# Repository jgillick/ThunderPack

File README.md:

# ThunderPack

A kick-ass microcontroller board with everything you need in a tiny package that fits in your pocket. Integrated battery & power management system, fast ARM microcontroller, USB bootloader, 4 high-power PWM outputs, 12 GPIOs, satisfying pushbutton switch, and more.

After years of wiring together portable LED controllers that all consisted of a lithium battery, charge controller, shitty slide power switch, and an Arduino nano (or similar), I wanted something better. I always found those versions to be janky and fragile -- not to mention concerned that damaging the pouch cell battery might make it explode in my pocket! This board has everything I need with room to expand.

* [Overview](https://github.com/jgillick/ThunderPack/wiki/)
* [Getting started](https://github.com/jgillick/ThunderPack/wiki/Getting-Started)
* [Pins & functions](https://github.com/jgillick/ThunderPack/wiki/Pinout-Details)
* [Example Programs](./examples)
* [Project log](https://hackaday.io/project/161054-lit-fist)

## Features

* Fast 96Mhz 32-bit ARM microcontroller ([STM32F11xx](https://www.st.com/resource/en/datasheet/stm32f411ce.pdf))
* Integrated high power 500mA lithium battery charger
* 4 high-current PWM outputs (1.4 - 2.3A per channel!) with an LED on each for debugging.
* Additional 12 GPIOs (USART, I2C, SPI, USB)
* 16MB onboard flash
* RGB DotStar LED
* Built-in USB
* Tactile on/off switch
* Momentary button with built-in debounce circuit
* Breadboard friendly
* Supports Arduino & CircuitPython.

## Board & Pinout

### v1.2 Compact
The newest & smallest Thunderpack, measuring in at a minuscule 4cm x 1.9cm (1.6 x 0.75 inches)! The PWM pins on this model can each drive 1.4A to ground (common cathode).

[See the full list of pins and details.](https://github.com/jgillick/ThunderPack/wiki/Pinout-Details)

### v1.2 Original
This is the original ThunderPack form factor and has the battery attached right to the circuit board. The PWM pins on this model can each drive 2.3A to ground (common cathode).

[See the full list of pins and details.](https://github.com/jgillick/ThunderPack/wiki/Pinout-Details)

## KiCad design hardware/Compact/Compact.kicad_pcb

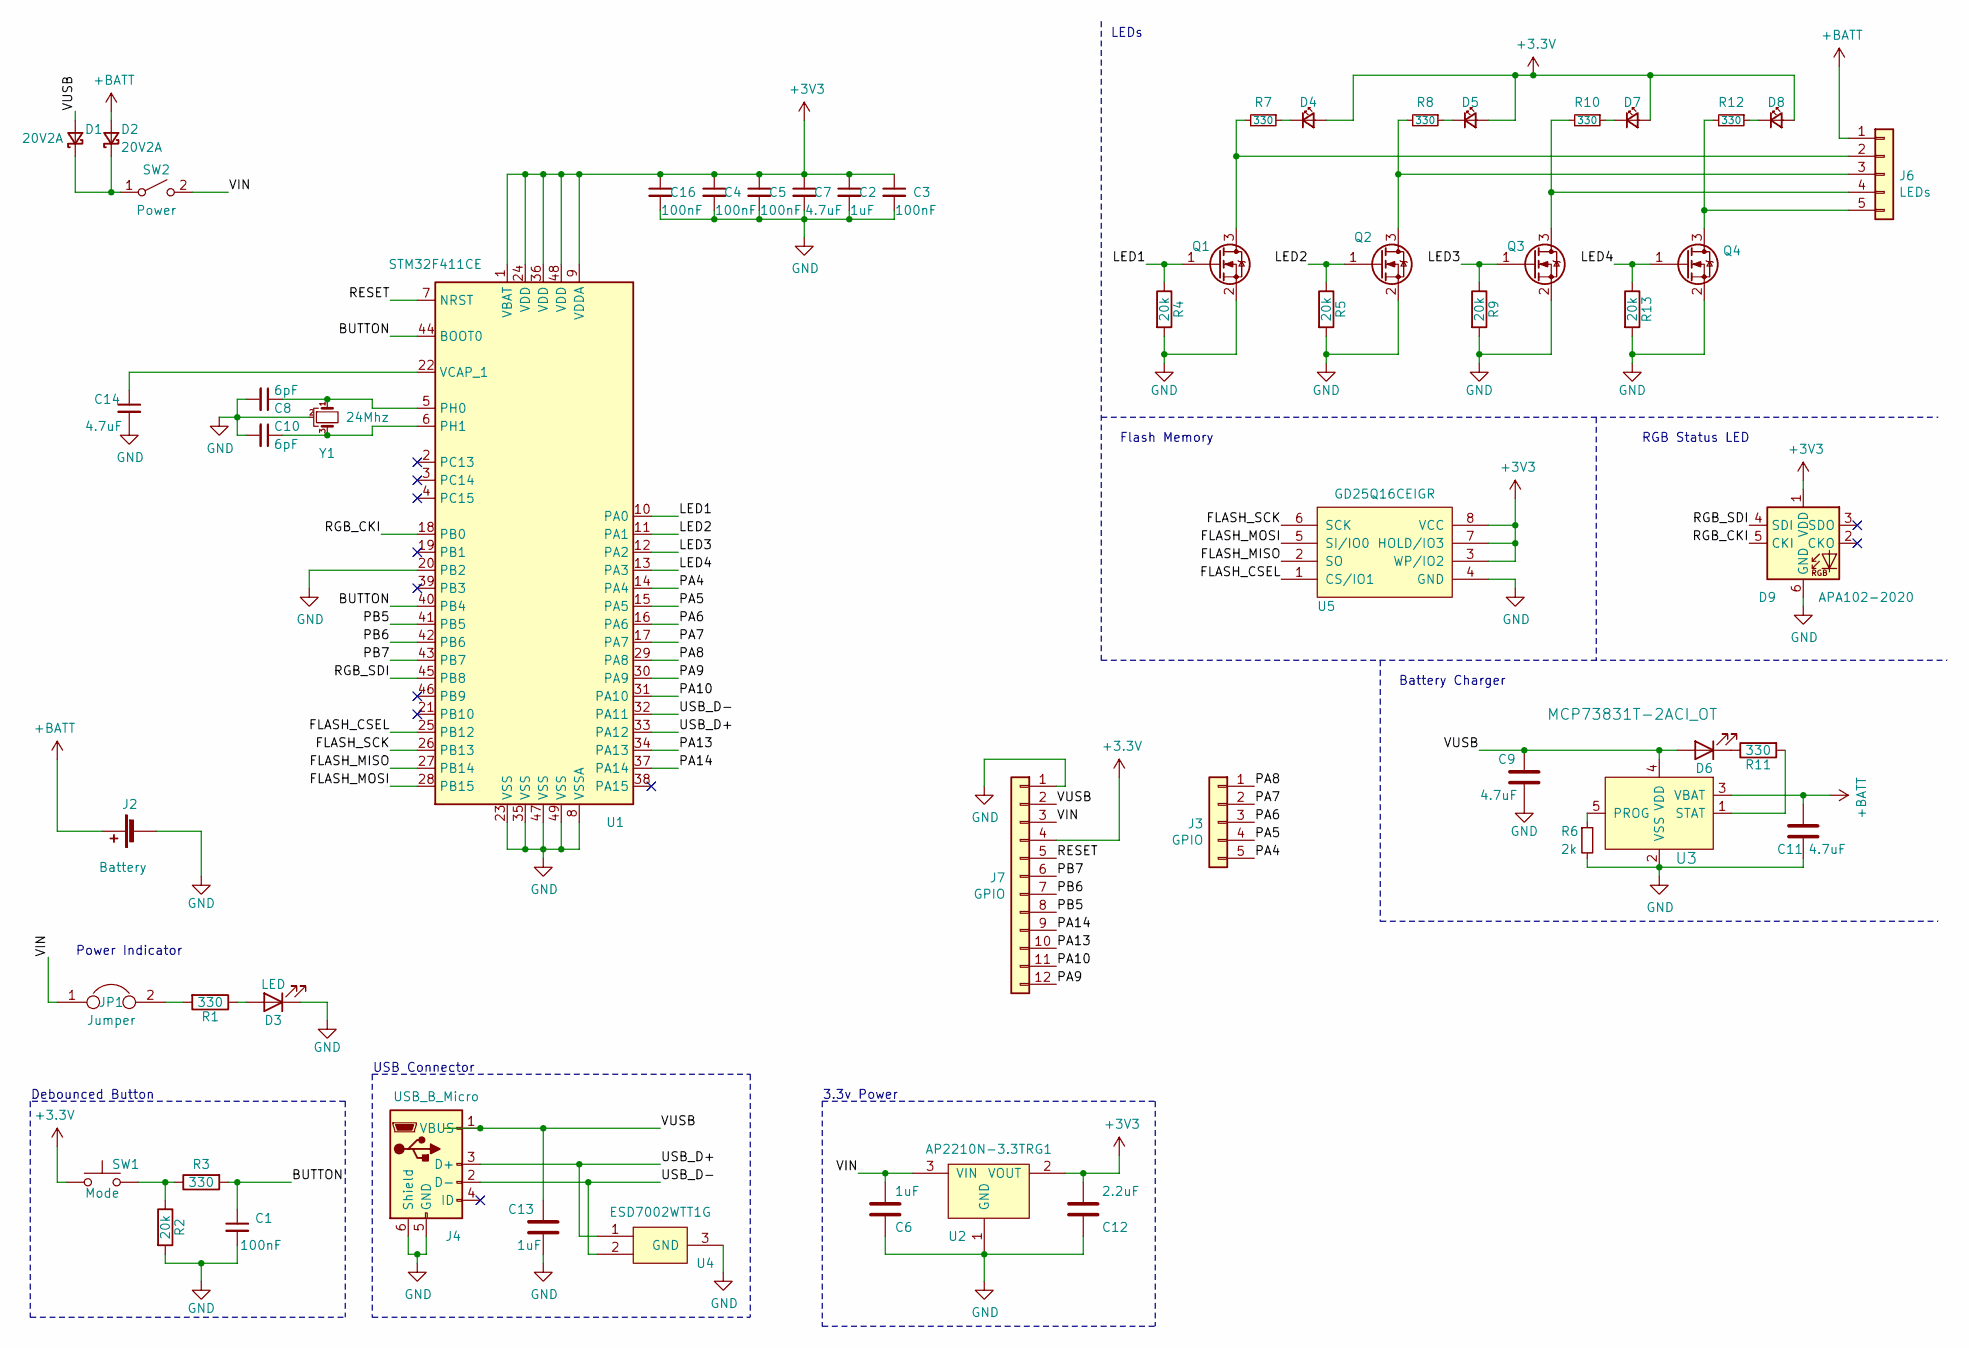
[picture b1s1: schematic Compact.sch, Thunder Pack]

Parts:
C1: 100nF; C_0603_1608Metric; MPN MF-CAP-0603-0.1uF
C2: 1uF; C_0603_1608Metric; MPN MF-CAP-0603-1uF
C3: 100nF; C_0603_1608Metric; MPN Yageo
C4, C5, C16: 100nF; C_0603_1608Metric; MPN 06035C104K4T2A
C6, C13: 1uF; C_0603_1608Metric
C7, C14: 4.7uF; C_0603_1608Metric; MPN CL10A475KO8NNNC‎
C8, C10: 6pF; C_0603_1608Metric; MPN CL10C060CB8NNNC; Digikey 1276-2133-1-ND
C9, C11: 4.7uF; C_0603_1608Metric
C12: 2.2uF; C_0603_1608Metric; MPN CL10A225KO8NNNC
D1, D2: 20V2A; D_SOD-323; MPN SMD22WS-TP
D3: LED; LED_0603_1608Metric_Castellated; MPN 150060BS55040
D4, D5, D7, D8: LED; LED_0603_1608Metric; MPN 150060VS75000
D6: LED; LED_0603_1608Metric; MPN 150060SS75000
D9: APA102-2020; LED-APA102-2020
J2: Battery; JST_PH_S2B-PH-K_1x02_P2.00mm_Horizontal; MPN Keystone 54; Digikey 36-54-ND
J3: GPIO; PinHeader_1x05_P2.54mm_Vertical
J4: USB_B_Micro; USB_Micro-B_Amphenol_10103594-0001LF_Horizontal; MPN 10103594-0001LF
J6: LEDs; PinHeader_1x05_P2.54mm_Vertical
J7: GPIO; PinHeader_1x12_P2.54mm_Vertical
JP1: Jumper; SolderJumper-2_P1.3mm_Bridged_RoundedPad1.0x1.5mm
Q1, Q2, Q3, Q4: BSS806N; SOT-323_SC-70; MPN BSS816NWH6327XTSA1
R1: 330; R_0603_1608Metric
R2, R4, R5, R9, R13: 20k; R_0603_1608Metric; MPN CR0603-FX-2002ELF
R3: 330; R_0603_1608Metric; MPN MF-RES-0603-330
R6: 2k; R_0603_1608Metric; MPN RMCF0603FT2K00
R7, R8, R10, R12: 330; R_0603_1608Metric; MPN CRCW0603270RJNEA
R11: 330; R_0603_1608Metric; MPN ERJ-PA3F4300V
SW1: Mode; SW_SPST_FSMSM; MPN 1437566-3; Digikey 450-1140-ND
SW2: Power; SW_KAN-15_SMD; MPN KAN15
U1: STM32F411CE; QFN-48-1EP_7x7mm_P0.5mm_EP5.6x5.6mm; MPN STM32F411CE
U2: AP2210N-3.3TRG1; SOT-23; MPN AP2210N-3.3TRG1
U3: MCP73831T-2ACI_OT; SOT-23-5; MPN MCP73831T-2ACI/OT; Digi-Key_PN MCP73831T-2ACI/OTCT-ND
U4: ESD7002WTT1G; SOT-323_SC-70
U5: GD25Q16CEIGR; DFN-8-1EP_3x2mm_P0.5mm_EP1.3x1.5mm
Y1: 24Mhz; Crystal_SMD_2016-4Pin_2.0x1.6mm; MPN XRCGB24M000F0L00R0; Digikey 490-5575-1-ND

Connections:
+BATT: C11.1, D2.2 (A), J2.1 (+), J6.1, U3.3 (VBAT)
/BUTTON: C1.1, R3.2, U1.40 (PB4), U1.44 (BOOT0)
/FLASH_CSEL: U1.25 (PB12), U5.1 (CS/IO1)
/FLASH_MISO: U1.27 (PB14), U5.2 (SO)
/FLASH_MOSI: U1.28 (PB15), U5.5 (SI/IO0)
/FLASH_SCK: U1.26 (PB13), U5.6 (SCK)
/LED1: Q1.1 (G), R4.1, U1.10 (PA0)
/LED2: Q2.1 (G), R5.1, U1.11 (PA1)
/LED3: Q3.1 (G), R9.1, U1.12 (PA2)
/LED4: Q4.1 (G), R13.1, U1.13 (PA3)
/PA4: J3.5, U1.14 (PA4)
/PA5: J3.4, U1.15 (PA5)
/PA6: J3.3, U1.16 (PA6)
/PA7: J3.2, U1.17 (PA7)
/PA8: J3.1, U1.29 (PA8)
/PA9: J7.12, U1.30 (PA9)
/PA10: J7.11, U1.31 (PA10)
/PA13: J7.10, U1.34 (PA13)
/PA14: J7.9, U1.37 (PA14)
/PB5: J7.8, U1.41 (PB5)
/PB6: J7.7, U1.42 (PB6)
/PB7: J7.6, U1.43 (PB7)
/RESET: J7.5, U1.7 (NRST)
/RGB_CKI: D9.5 (CKI), U1.18 (PB0)
/RGB_SDI: D9.4 (SDI), U1.45 (PB8)
/USB_D+: J4.3 (D+), U1.33 (PA12), U4.1
/USB_D-: J4.2 (D-), U1.32 (PA11), U4.2
/VIN: C6.1, J7.3, JP1.1, SW2.2 (B), U2.3 (VIN)
/VUSB: C9.1, C13.2, D1.2 (A), D6.2 (A), J4.1 (VBUS), J7.2, U3.4 (VDD)
GND: C1.2, C2.2, C3.2, C4.2, C5.2, C6.2, C7.2, C8.2, C9.2, C10.2, C11.2, C12.2, C13.1, C14.2, C16.2, D3.1 (K), D9.6 (GND), J2.2 (-), J4.5 (GND), J4.6 (Shield), J7.1, Q1.2 (S), Q2.2 (S), Q3.2 (S), Q4.2 (S), R2.2, R4.2, R5.2, R6.2, R9.2, R13.2, U1.8 (VSSA), U1.20 (PB2), U1.23 (VSS), U1.35 (VSS), U1.47 (VSS), U1.49 (VSS), U2.1 (GND), U3.2 (VSS), U4.3 (GND), U5.4 (GND), Y1.2
unnamed: C8.1, U1.5 (PH0), Y1.1
unnamed: C10.1, U1.6 (PH1), Y1.3
unnamed: C14.1, U1.22 (VCAP_1)
unnamed: D1.1 (K), D2.1 (K), SW2.1 (A)
unnamed: D3.2 (A), R1.1
unnamed: D4.1 (K), R7.1
unnamed: D5.1 (K), R8.1
unnamed: D6.1 (K), R11.1
unnamed: D7.1 (K), R10.1
unnamed: D8.1 (K), R12.1
unnamed: J6.2, Q1.3 (D), R7.2
unnamed: J6.3, Q2.3 (D), R8.2
unnamed: J6.4, Q3.3 (D), R10.2
unnamed: J6.5, Q4.3 (D), R12.2
unnamed: JP1.2, R1.2
unnamed: R2.1, R3.1, SW1.2
unnamed: R6.1, U3.5 (PROG)
unnamed: R11.2, U3.1 (STAT)

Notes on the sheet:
Battery Charger
USB Connector
LEDs
3.3v Power
Power Indicator
RGB Status LED
Flash Memory
Debounced Button

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
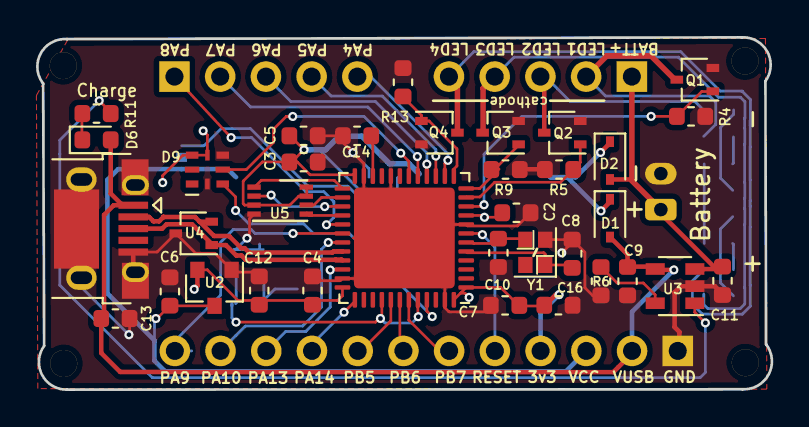
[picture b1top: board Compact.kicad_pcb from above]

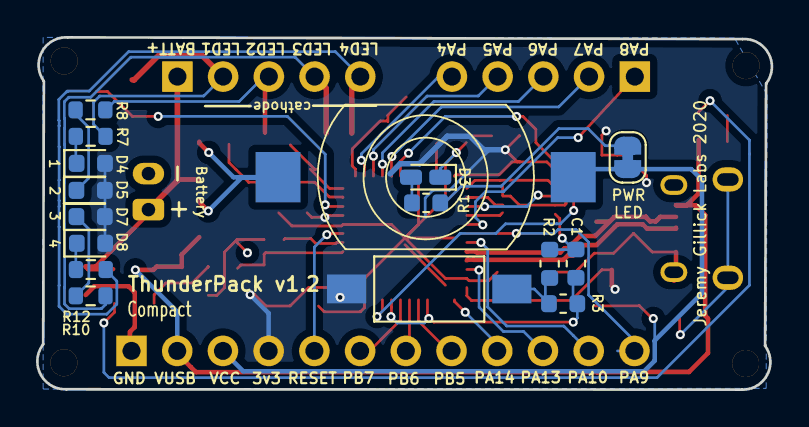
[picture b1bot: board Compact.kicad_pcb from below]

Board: 2 copper layers, 40.8 x 19.6 mm, 55 parts (16 on the bottom side), 49 nets.

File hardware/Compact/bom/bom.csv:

Id,Designator,Manufacturer,Quantity,*Mfg Part #,Value,Package,Description / Value,Type,Notes,
1,U4,ON Semiconductor,1,ESD7002WTT1G,,SOT-323_SC-70,TVS DIODE 5V SC70-3,SMD,,
2,D9,SparkFun Electronics,1,APA102-2020,,LED-APA102-2020,ADDRESS LED STRIP SER RGB 10PK,SMD,,
3,J2,TE Connectivity,1,440055-2,,JST_PH_S2B-PH-K_1x02_P2.00mm_Horizontal,"Connector Header Through Hole, Right Angle 2 position 0.079"" (2.00mm)",thru-hole,,
4,"R12,R10,R8,R7,R3,R11,R1",,7,,330,0603,RES SMD 330 OHM 0.5% 1/5W 0603,SMD,,
5,D6,Würth Elektronik,1,150060SS75000,,0603,LED RED CLEAR 0603 SMD,SMD,,
6,"D8,D7,D5,D4",Würth Elektronik,4,150060VS75000,,0603,LED GREEN CLEAR 0603 SMD,SMD,,
7,"D1,D2",Micro Commercial Co,2,SMD22WS-TP,,SOD-323,"2A,20V,SCHOTTKY,SOD-323 PACKAGE",SMD,,
8,SW1,TE Connectivity,1,FSMSM,,,SWITCH TACTILE SPST-NO 0.05A 24V,SMD,,
9,U5,GigaDevice Semiconductor,1,GD25Q16CEIGR,,8-XFDFN,FLASH - NOR Memory IC 16Mb (2M x 8) SPI - Quad I/O 120MHz 8-USON (2x3),SMD,,
10,U1,STMicroelectronics,1,STM32F411CEU6,,48-UFQFN,IC MCU 32BIT 512KB FLSH 48UFQFPN,SMD,,
11,"Q2,Q4,Q3,Q1",Infineon Technologies,4,BSS816NWH6327XTSA1,,SOT-323,MOSFET N-CH 20V 1.4A SOT323-3,SMD,,
12,"R13,R9,R5,R4,R2",,5,,20k,0603,RES SMD 20K OHM 0.5% 1/10W 0603,SMD,,
13,"C1,C4,C16,C5,C3",,5,,100nF,0603,CAP CER 0.1UF 50V X7R 0603,SMD,,
14,U3,Microchip Technology,1,MCP73831T-2ACI/OT,,SOT-23-5,IC BATT CNTL LI-ION 1CEL SOT23-5,SMD,,
15,R6,,1,,2k,0603,RES 2K OHM 1% 1/10W 0603,SMD,,
16,"C11,C9,C14,C7",,4,,4.7uF,0603,CAP CER 4.7UF 16V X5R 0603,SMD,,
17,D3,Würth Elektronik,1,150060BS55040,,0603,LED BLUE DIFFUSED 0603 SMD,SMD,,
18,C12,,1,,2.2uF,0603,CAP CER 2.2UF 16V X5R 0603,SMD,,
19,Y1,XRCGB24M000F0L00R0,1,24Mhz,,4-SMD,CRYSTAL 24.0000MHZ 6PF SMD,SMD,,
20,U2,Diodes Incorporated,1,AP2210N-3.3TRG1,,SOT-23-3,IC REG LINEAR 3.3V 300MA SOT23-3,SMD,,
21,J4,Amphenol ICC (FCI),1,10103594-0001LF,,,CONN RCPT USB2.0 MICRO B SMD R/A,SMD,,
22,"C13,C6,C2",,3,,1uF,0603,CAP CER 1UF 25V X5R 0603,SMD,,
23,"C10,C8",,2,,6pF,0603,CAP CER 6PF 50V C0G/NP0 0603,SMD,,

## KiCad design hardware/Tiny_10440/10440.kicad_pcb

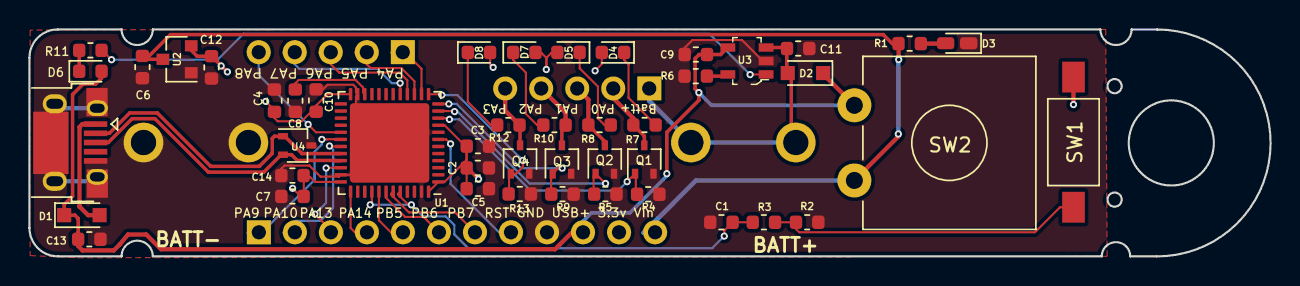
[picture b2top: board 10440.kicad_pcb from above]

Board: 2 copper layers, 87.5 x 16.0 mm, 50 parts (0 on the bottom side), 40 nets.

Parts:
C1: 100nF; C_0603_1608Metric
C2, C6, C13: 1uf; C_0603_1608Metric
C3, C4, C5, C10, C14: 100nf; C_0603_1608Metric
C7, C8, C9, C11: 4.7uF; C_0603_1608Metric
C12: 2.2uF; C_0603_1608Metric
D1, D2: 20V2A; D_SOD-323_HandSoldering
D3: LED; LED_0603_1608Metric_Castellated
D4, D5, D6, D7, D8: LED; LED_0603_1608Metric
J2: Battery; MDP_BK-82_10440
J3: GPIO; PinHeader_1x05_P2.54mm_Vertical
J4: USB_B_Micro; USB_Micro-B_Amphenol_10103594-0001LF_Horizontal
J5: LEDs; PinHeader_1x05_P2.54mm_Vertical
J7: GPIO/Power; PinHeader_1x12_P2.54mm_Vertical
Q1, Q2, Q3, Q4: BSS806N; SOT-323_SC-70
R1, R7, R8, R10, R12: 270; R_0603_1608Metric
R2: 20K; R_0603_1608Metric
R3, R11: 330; R_0603_1608Metric
R4, R5, R9, R13: 20k; R_0603_1608Metric
R6: 675; R_0603_1608Metric
SW1: Mode; SW_SPST_FSMSM
SW2: Power; SW_CW_GPTS203211B
U1: STM32F412CGUx; QFN-48-1EP_7x7mm_P0.5mm_EP5.6x5.6mm
U2: AP2210N-3.3TRG1; SOT-23
U3: MCP73831T-2ACI_OT; SOT-753
U4: ESD7002WTT1G; SOT-323_SC-70

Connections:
+3V3: C2.1, C3.1, C4.1, C5.1, C7.1, C10.1, C12.1, C14.1, D4.2, D5.2, D7.2, D8.2, J7.11, SW1.1, U1.1, U1.9, U1.24, U1.36, U1.48, U2.2
+BATT: C11.1, D2.2, J2.1, J5.1, U3.3
/BUTTON: C1.1, R3.2, U1.40, U1.44
/LED1: J5.2, Q1.3, R7.2
/LED2: J5.3, Q2.3, R8.2
/LED3: J5.4, Q3.3, R10.2
/LED4: J5.5, Q4.3, R12.2
/PA4: J3.1, U1.14
/PA5: J3.2, U1.15
/PA6: J3.3, U1.16
/PA7: J3.4, U1.17
/PA8: J3.5, U1.29
/PA9: J7.1, U1.30
/PA10: J7.2, U1.31
/PA13: J7.3, U1.34
/PA14: J7.4, U1.37
/PB5: J7.5, U1.41
/PB6: J7.6, U1.42
/PB7: J7.7, U1.43
/PWM1: Q1.1, R4.1, U1.10
/PWM2: Q2.1, R5.1, U1.11
/PWM3: Q3.1, R9.1, U1.12
/PWM4: Q4.1, R13.1, U1.13
/RESET: J7.8, U1.7
/USB_D+: J4.3, U1.33, U4.2
/USB_D-: J4.2, U1.32, U4.1
/VIN: C6.1, J7.12, R1.2, SW2.2, U2.3
/VUSB: C9.1, C13.2, D1.1, D2.1, D6.2, J7.10, SW2.1, U3.4
GND: C1.2, C2.2, C3.2, C4.2, C5.2, C6.2, C7.2, C8.2, C9.2, C10.2, C11.2, C12.2, C13.1, C14.2, D3.1, J2.2, J4.5, J4.6, J7.9, Q1.2, Q2.2, Q3.2, Q4.2, R2.2, R4.2, R5.2, R6.2, R9.2, R13.2, U1.8, U1.23, U1.35, U1.47, U1.49, U2.1, U3.2, U4.3
unnamed: C8.1, U1.22
unnamed: D1.2, J4.1
unnamed: D3.2, R1.1
unnamed: D4.1, R7.1
unnamed: D5.1, R8.1
unnamed: D6.1, R11.1
unnamed: D7.1, R10.1
unnamed: D8.1, R12.1
unnamed: R2.1, R3.1, SW1.2
unnamed: R6.1, U3.5
unnamed: R11.2, U3.1

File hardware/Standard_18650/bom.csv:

Id,RefDefs,Package,Qty,Value,part number/description,,
1,U1,QFN-48-1EP_7x7mm_P0.5mm_EP5.6x5.6mm,1,,STM32F412CGU6,,
2,R6,603,1,675R,,,
3,J2,,1,,Keystone Electronics 54,,
4,"C1,C16,C15,C4,C3,C5",603,5,100nF,,,
5,"C14,C7",603,2,4.7uF,,,
6,U3,SOT-23-6,1,,BQ21040DBVR,,
7,D6,603,1,,150060BS55040,,
8,"D8,D7,D5,D4",603,4,,150060VS75000,,
9,R14,603,1,10k,,,
10,"R11,R3",603,2,330R,,,
11,"C9,C11,C12,C13,C6,C2",603,4,1uF,,,
12,U4,SOT-323_SC-70,1,,ESD7002WTT1G,,
13,U2,SOT-23,1,,AP2210N-3.3TRG1,,
14,J4,,1,,Amphenol 10103594-0001LF USB micro,,
15,SW2,,1,,GPTS203211B,,
16,SW1,,1,,TE Connectivity FSMSM - SWITCH TACTILE SPST-NO 0.05A 24V,,
17,"D1,D2",D_SOD-323,2,,"2A,20V,SCHOTTKY,SOD-323 PACKAGE",,
18,L1,603,1,Bead,BLM18TG601TN1D - Ferrite bead - 600 Ohms @ 100MHz 1 Ferrite Bead 0603 (1608 Metric) 200mA 450mOhm,,
19,"R1,R7,R8,R10,R12",603,5,270R,,,
20,"R2,R4,R5,R9,R13",603,4,20k,,,
21,"Q1,Q3,Q4,Q2",SOT-23,4,,BSS806NH6327XTSA1,,
22,D3,603,1,,150060SS75000,,

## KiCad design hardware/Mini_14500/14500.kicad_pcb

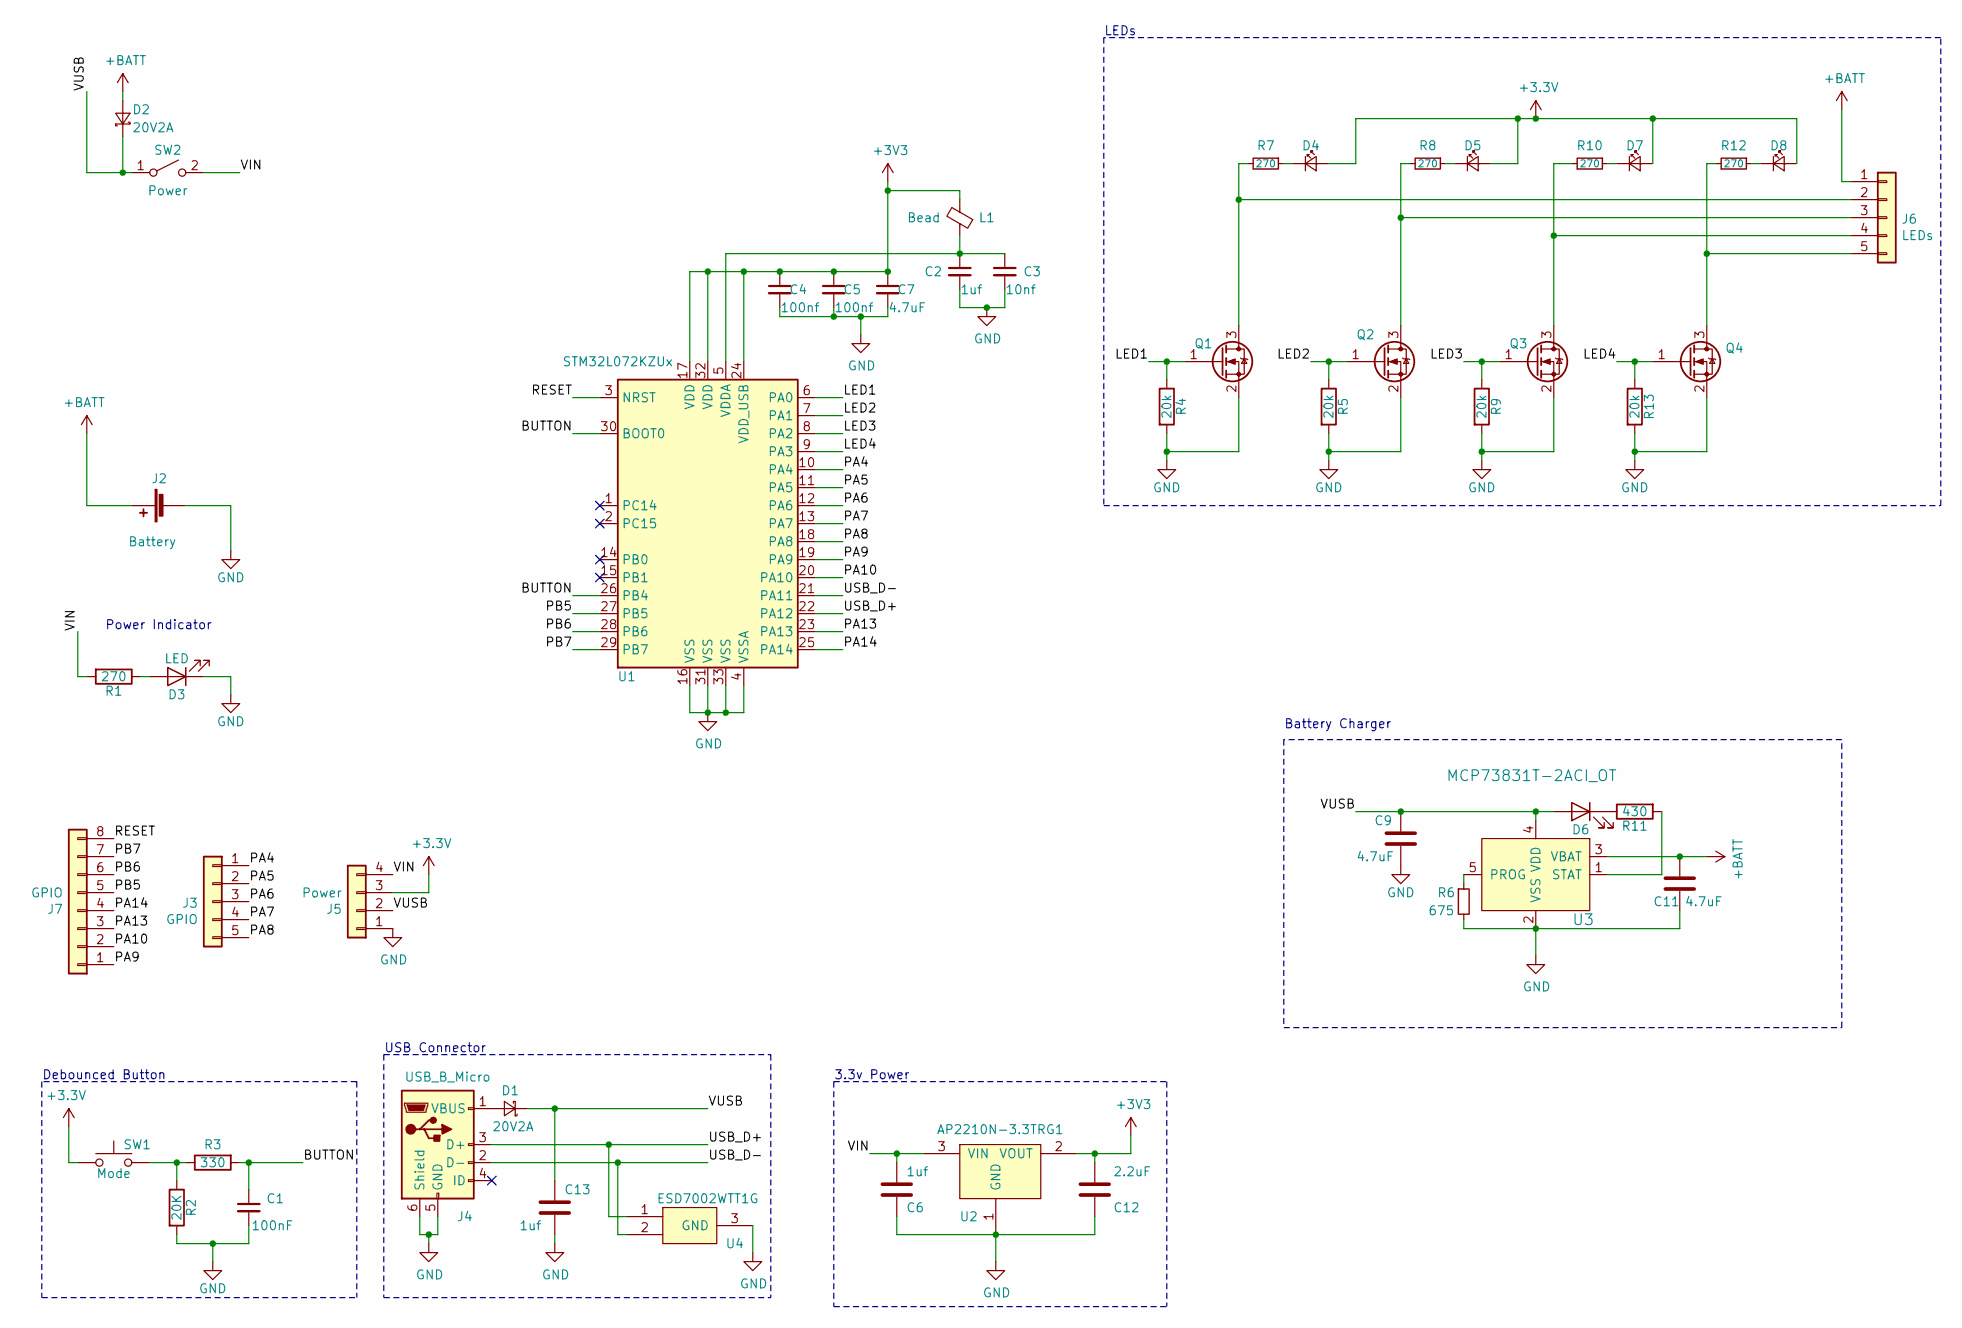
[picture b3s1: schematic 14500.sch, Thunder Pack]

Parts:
C1: 100nF; C_0603_1608Metric; MPN MF-CAP-0603-0.1uF
C2: 1uf; C_0603_1608Metric; MPN MF-CAP-0603-1uF
C3: 10nf; C_0603_1608Metric; MPN Yageo
C4, C5: 100nf; C_0603_1608Metric; MPN 06035C104K4T2A
C6, C13: 1uf; C_0603_1608Metric
C7: 4.7uF; C_0603_1608Metric; MPN CL10A475KO8NNNC‎
C9, C11: 4.7uF; C_0603_1608Metric
C12: 2.2uF; C_0603_1608Metric
D1, D2: 20V2A; D_SOD-323_HandSoldering; MPN SMD22WS-TP
D3: LED; LED_0603_1608Metric_Castellated; MPN 150060SS75000
D4, D5, D7, D8: LED; LED_0603_1608Metric; MPN 150060VS75000
D6: LED; LED_0603_1608Metric; MPN 150060BS55040
J2: Battery; MDP_BK-82_14500; MPN Keystone 54; Digikey 36-54-ND
J3: GPIO; PinHeader_1x05_P2.54mm_Vertical
J4: USB_B_Micro; USB_Micro-B_Amphenol_10103594-0001LF_Horizontal; MPN 10103594-0001LF
J5: Power; PinHeader_1x04_P2.54mm_Vertical
J6: LEDs; PinHeader_1x05_P2.54mm_Vertical
J7: GPIO; PinHeader_1x08_P2.54mm_Vertical
L1: Bead; L_0603_1608Metric; MPN BLM18TG601TN1D; Digikey 490-9702-1-ND
Q1, Q2, Q3, Q4: BSS806N; SOT-23; MPN BSS806NH6327XTSA1
R1: 270; R_0603_1608Metric
R2: 20K; R_0603_1608Metric; MPN CR0603-FX-2002ELF
R3: 330; R_0603_1608Metric; MPN MF-RES-0603-330
R4, R5, R9, R13: 20k; R_0603_1608Metric; MPN CR0603-FX-2002ELF
R6: 675; R_0603_1608Metric
R7, R8, R10, R12: 270; R_0603_1608Metric; MPN CRCW0603270RJNEA
R11: 430; R_0603_1608Metric; MPN ERJ-PA3F4300V
SW1: Mode; SW_SPST_FSMSM; MPN 1437566-3; Digikey 450-1140-ND
SW2: Power; SW_CW_GPTS203211B; MPN GPTS203211B
U1: STM32L072KZUx; QFN-32-1EP_5x5mm_P0.5mm_EP3.45x3.45mm
U2: AP2210N-3.3TRG1; SOT-23; MPN AP2210N-3.3TRG1
U3: MCP73831T-2ACI_OT; SOT-753; MPN MCP73831T-2ACI/OT; Digi-Key_PN MCP73831T-2ACI/OTCT-ND
U4: ESD7002WTT1G; SOT-323_SC-70; MPN ESD7002WTT1G

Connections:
+BATT: C11.1, D2.2 (A), J2.1 (+), J6.1, U3.3 (VBAT)
/BUTTON: C1.1, R3.2, U1.26 (PB4), U1.30 (BOOT0)
/LED1: Q1.1 (G), R4.1, U1.6 (PA0)
/LED2: Q2.1 (G), R5.1, U1.7 (PA1)
/LED3: Q3.1 (G), R9.1, U1.8 (PA2)
/LED4: Q4.1 (G), R13.1, U1.9 (PA3)
/PA4: J3.1, U1.10 (PA4)
/PA5: J3.2, U1.11 (PA5)
/PA6: J3.3, U1.12 (PA6)
/PA7: J3.4, U1.13 (PA7)
/PA8: J3.5, U1.18 (PA8)
/PA9: J7.1, U1.19 (PA9)
/PA10: J7.2, U1.20 (PA10)
/PA13: J7.3, U1.23 (PA13)
/PA14: J7.4, U1.25 (PA14)
/PB5: J7.5, U1.27 (PB5)
/PB6: J7.6, U1.28 (PB6)
/PB7: J7.7, U1.29 (PB7)
/RESET: J7.8, U1.3 (NRST)
/USB_D+: J4.3 (D+), U1.22 (PA12), U4.1
/USB_D-: J4.2 (D-), U1.21 (PA11), U4.2
/VIN: C6.1, J5.4, R1.2, SW2.2 (B), U2.3 (VIN)
/VUSB: C9.1, C13.2, D1.1 (K), D2.1 (K), D6.2 (A), J5.2, SW2.1 (A), U3.4 (VDD)
GND: C1.2, C2.2, C3.2, C4.2, C5.2, C6.2, C7.2, C9.2, C11.2, C12.2, C13.1, D3.1 (K), J2.2 (-), J4.5 (GND), J4.6 (Shield), J5.1, Q1.2 (S), Q2.2 (S), Q3.2 (S), Q4.2 (S), R2.2, R4.2, R5.2, R6.2, R9.2, R13.2, U1.4 (VSSA), U1.16 (VSS), U1.31 (VSS), U1.33 (VSS), U2.1 (GND), U3.2 (VSS), U4.3 (GND)
unnamed: C2.1, C3.1, L1.1, U1.5 (VDDA)
unnamed: D1.2 (A), J4.1 (VBUS)
unnamed: D3.2 (A), R1.1
unnamed: D4.1 (K), R7.1
unnamed: D5.1 (K), R8.1
unnamed: D6.1 (K), R11.1
unnamed: D7.1 (K), R10.1
unnamed: D8.1 (K), R12.1
unnamed: J6.2, Q1.3 (D), R7.2
unnamed: J6.3, Q2.3 (D), R8.2
unnamed: J6.4, Q3.3 (D), R10.2
unnamed: J6.5, Q4.3 (D), R12.2
unnamed: R2.1, R3.1, SW1.2
unnamed: R6.1, U3.5 (PROG)
unnamed: R11.2, U3.1 (STAT)

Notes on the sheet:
Battery Charger
USB Connector
Power Indicator
LEDs
Debounced Button
3.3v Power

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
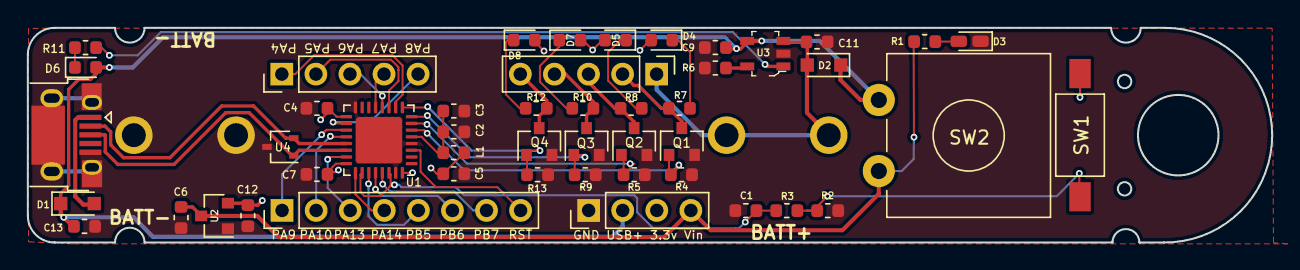
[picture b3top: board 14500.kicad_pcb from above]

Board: 2 copper layers, 92.8 x 16.0 mm, 49 parts (0 on the bottom side), 40 nets.

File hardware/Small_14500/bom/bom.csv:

Id,RefDefs,Package,Qty,Value,part number/description,,
1,Y1,4-SMD,1,24Mhz,XRCGB24M000F0L00R0,,
2,"C16,C15",603,2,6pF,CL10C060CB8NNNC,,
3,R6,603,1,680R,,,
4,D6,603,1,,150060BS55040,,
5,"D8,D7,D5,D4",603,4,,150060VS75000,,
6,"R11,R3",603,2,330R,,,
7,"C11,C8,C9,C7",603,4,4.7uF,CC0603KRX5R5BB475,,
8,U4,SOT-323_SC-70,1,,ESD7002WTT1G,,
9,"C12,C13,C6,C2",603,4,1uf,,,
10,U2,SOT-23,1,,AP2210N-3.3TRG1,,
11,J4,USB_B_Micro,1,,Amphenol 10103594-0001LF,,
12,SW2,Through hole,1,,GPTS203211B,,
13,SW1,Through hole,1,,TE Connectivity FSMSM,,
14,"R2,R4,R5,R9,R13",603,5,20k,,,
15,"R12,R1,R7,R8,R10",603,5,270R,,,
16,"Q3,Q2,Q1,Q4",SOT-23,4,,BSS806N,,
17,D3,603,1,LED,150060SS75000,,
18,"C1,C5,C14,C10,C4,C3",603,6,100nF,,,
19,U1,QFN-48-1EP_7x7mm_P0.5mm_EP5.6x5.6mm,1,,STM32F411CEU6,,
20,U3,SOT-753,1,,MCP73831T-2ACI_OT,,
21,"D1,D2",D_SOD-323,2,20V2A,SMD22WS-TP,,
22,L1,603,1,,BLM18TG601TN1D,,

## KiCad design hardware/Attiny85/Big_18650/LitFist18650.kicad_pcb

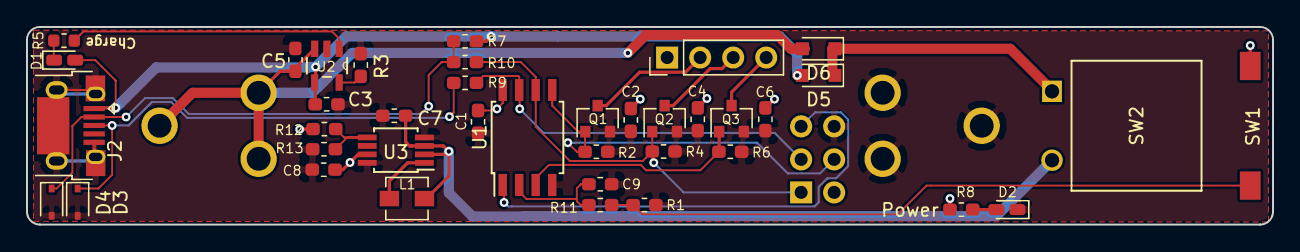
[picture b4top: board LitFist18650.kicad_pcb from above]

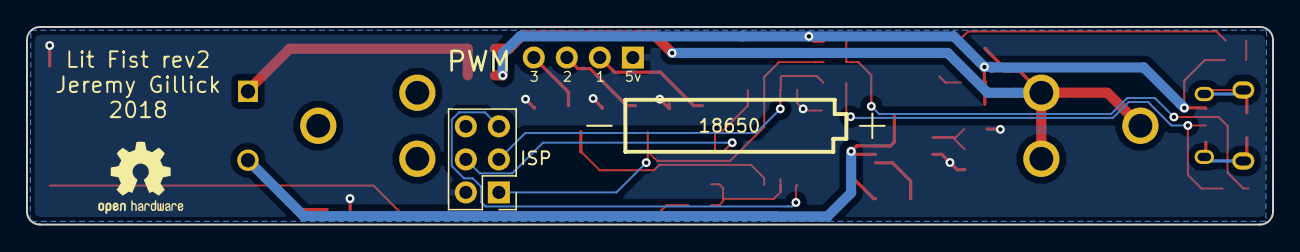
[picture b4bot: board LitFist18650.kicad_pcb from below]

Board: 2 copper layers, 95.8 x 15.2 mm, 41 parts (2 on the bottom side), 24 nets.

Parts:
C1, C9: 0.1uF; C_0603_1608Metric_Pad1.05x0.95mm_HandSolder
C2, C3, C4, C5, C6: 4.7uF; C_0603_1608Metric_Pad1.05x0.95mm_HandSolder
C7: 10uF; C_0603_1608Metric_Pad1.05x0.95mm_HandSolder
C8: 22uF; C_0603_1608Metric_Pad1.05x0.95mm_HandSolder
D1, D2: LED; LED_0603_1608Metric_Castellated
D3, D4: 3v6; D_SOD-323
D5, D6: 20V2A; D_SOD-323_HandSoldering
J1: PWM; PinHeader_1x04_P2.54mm_Vertical
J2: USB_B_Micro; USB_Micro-B_Amphenol_10103594-0001LF_Horizontal
J3: Battery; Battery_Clips_18650
J4: ISP; PinHeader_2x03_P2.54mm_Vertical
L1: 2.2uH3A; L_Vishay_IHLP-1212
Q1, Q2, Q3: NTR4003NT1G; SOT-23
R1: 20K; R_0603_1608Metric_Pad1.05x0.95mm_HandSolder
R2, R4, R6: 20k; R_0603_1608Metric_Pad1.05x0.95mm_HandSolder
R3: 2k; R_0603_1608Metric_Pad1.05x0.95mm_HandSolder
R5: 470; R_0603_1608Metric
R7: 2.2k; R_0603_1608Metric_Pad1.05x0.95mm_HandSolder
R8: 120; R_0603_1608Metric_Pad1.05x0.95mm_HandSolder
R9, R10: 68; R_0603_1608Metric_Pad1.05x0.95mm_HandSolder
R11: 330; R_0603_1608Metric_Pad1.05x0.95mm_HandSolder
R12: 750K; R_0603_1608Metric_Pad1.05x0.95mm_HandSolder
R13: 100K; R_0603_1608Metric_Pad1.05x0.95mm_HandSolder
SW1: Mode; Switch_TE_FSMSM
SW2: Power; Switch_SPST_GPTS203211BR2
U1: ATtiny85-20SU; SOIJ-8_5.3x5.3mm_P1.27mm
U2: MCP73831T-2ACI/OT; SOT95P280X145-5N
U3: PAM2401-8MSOP; MSOP-8_3x3mm_P0.65mm

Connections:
+5V: C1.1, C2.2, C4.2, C6.2, C8.1, J1.1, J4.2, R8.2, R12.1, SW1.2, U1.8, U3.7
+BATT: C5.1, D6.2, J3.1, U2.3
D+: J4.3, R9.1, U1.7
D-: J4.1, Q2.1, R4.1, R10.1, U1.6
GND: C1.2, C2.1, C3.2, C4.1, C5.2, C6.1, C7.2, C8.2, C9.2, D2.1, D3.2, D4.2, J2.5, J2.6, J3.2, J4.6, Q1.2, Q2.2, Q3.2, R1.2, R2.2, R3.2, R4.2, R6.2, R13.2, U1.4, U2.2, U3.4, U3.8
MOSI: J4.4, Q1.1, R2.1, U1.5
unnamed: C7.1, L1.1, SW2.2, U3.2, U3.3
unnamed: C9.1, R11.2, U1.2
unnamed: D1.1, R5.2
unnamed: D2.2, R8.1
unnamed: D3.1, J2.3, R9.2
unnamed: D4.1, J2.2, R7.1, R10.2
unnamed: D5.1, D6.1, SW2.1
unnamed: J1.2, Q1.3
unnamed: J1.3, Q2.3
unnamed: J1.4, Q3.3
unnamed: L1.2, U3.1
unnamed: R1.1, R11.1, SW1.1
unnamed: R3.1, U2.5
unnamed: R5.1, U2.1
unnamed: R12.2, R13.1, U3.5
PWM3: Q3.1, R6.1, U1.3
RST: J4.5, U1.1
Vin: C3.1, D1.2, D5.2, J2.1, R7.2, U2.4

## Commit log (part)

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2018-09-03 Add hardware
2018-09-04 Upgrade to kicad 5
2018-09-13 Populate PCB with ALL THE NEW THINGS
2018-09-13 Remove VCC
2018-09-14 Finish routing
2018-09-14 Adjust routing
2018-09-18 misc
2018-09-18 Move hardware files
2018-09-18 Rename hardware files
2018-09-18 Fix battery number from 8650 to 18650
2018-09-18 misc save
2018-10-22 Fix Attiny footprint. Add debounce circuit.
2018-10-28 Move Attiny version of hardware
2018-10-29 minor save
2018-10-29 Add STM32
2018-10-30 Annotations
2018-10-31 Basic schematic
2018-10-31 Update LED circuit
2019-05-07 PCB for fab
2019-09-06 Update hardware
2019-09-06 Cleanup example & makefile
2019-09-06 Fix ChibiOS name casing.
2019-09-06 Cleanup and docs.
2019-09-07 Update config and docs.
2019-09-07 Move kicad files.
2019-09-07 Docs
2019-09-07 Remove attiny hardware.
2019-09-07 More docs
2019-09-07 Add better description and features section.
2019-09-07 Add blink example.
2019-09-07 Update to use updated board.h definitions.
2019-09-07 Add button example
2019-09-07 Cleanup
2019-09-08 Add 'flash-dfu' make rule.
2019-09-08 Add examples: Fade & RunningLEDs
2019-09-08 Tweak settings.
2019-09-09 Rename LitFist to Thunder Pack
2019-09-09 Ignore more.
2019-09-09 Add arduino support.
2019-09-09 Update LED numbers
2019-09-09 Update features.
2019-09-10 Simplify the Makefile used in each example.
2019-09-10 Add USB serial example.
2019-09-10 Add libopencm3 examples directory
2019-09-10 Add a full 10-pin JTAG connector.
2019-09-11 Change to 32 pin package.
2019-09-11 Add top labels and cleanup.
2019-09-11 Add working libopencm3 examples.
2019-09-11 Update copy.
2019-09-11 Update part number
2019-09-11 Cleanup features list.
2019-09-11 Cleanup.
2019-09-11 Use standard parts/symbols
2019-09-12 Update charger IC (MCP73833-AMI_UN)
2019-09-12 Add PWM fade example to libopencm3. Fix make files.
2019-09-12 Add chip reference docs
2019-09-13 Attempt to remove unnecessary things.
2019-09-13 Fix spacing
2019-09-13 Add the correct datasheet.
2019-09-13 Rename directory
2019-09-13 Get simplified fade program working.
2019-09-13 Cleanup code.
2019-09-13 rename shared to lib
2019-09-14 Move board files.
2019-09-14 partial upgrade.
2019-09-14 Add latest version of ChibiOS as submodule.
2019-09-14 Rename shared to common
2019-09-14 Cleanup makefile.
2019-09-14 Update makefiles.
2019-09-14 Checkpoint.
2019-09-14 Progress?
2019-09-15 Fix compile
2019-09-15 Get "MultiplePrograms" program compiling.
2019-09-15 Rename "Drivers" to "drivers"
2019-09-16 Add check to verify the ChibiOS library has been initialized.
2019-09-16 Chibios upgrade (#1)
2019-09-17 Add STM32Cube
2019-09-17 Add "Fade" and move files around.
2019-09-17 Copy changes.
2019-09-17 More USB Serial (CDC) examples.
2019-09-17 Update arduino instructions.
2019-09-17 Make PCB labels bigger. Export gerbers.
2019-09-18 Add EEPROM example.
2019-09-18 Update trace
2019-09-18 Add EEPROM examples to libopencm3
2019-09-18 EEPROM Arduino example
2019-09-18 USBSerial example for STM32Cube
2019-09-20 Convert PCB from 4 layer to 2 layer.
2019-09-21 Add EEPROM example to ChibiOS
2019-09-21 Cleanup readme files
2019-09-21 Typo
2019-09-21 Fix path to libopencm3
2019-09-21 cleanup spaces
2019-09-30 Add Images to readme.
2019-09-30 Fix images.
2019-09-30 Fix max width
2019-09-30 Git strips max-width.
2019-09-30 More / better copy.
2019-10-04 Move JTAG to GPIOs
2019-10-04 New gerbers.
2019-10-05 Add more notches for attachment.
2019-10-05 Add interactive BOM
2019-10-08 Adjust battery position.
2019-10-08 Give battery more room
2019-10-08 Add mounting notches and holes
2019-10-14 Create board pinout graphic
2019-10-14 Add pinout to README.
2019-10-14 Convert 4 layer -> 2 layer PCB (#2)
2019-10-14 Update pinout markup.
2019-10-14 Fix link to PNG.
2019-10-14 Add circuit schematic
2019-10-14 Add name/rev to pinout images
2019-10-14 Add power to legend
2019-10-14 Fix USB pin line
2019-10-14 Add link to datasheet.
2019-10-15 Hardware feedback.
2019-10-17 Add running LEDs to arduino examples
2019-10-17 Change USB TVS.
2019-10-21 Fix arduino sketch name.
2019-10-21 Change battery changing controller
2019-10-22 Add USART, I2C & SPI pins to silkscreen
2019-11-04 Add addressable LED example to STM32Cube
2019-11-04 ws2812b API documentation.
2019-11-06 Change BATT+ to Vin
2019-11-06 Add EEPROM to features. Links to wiki.
2019-11-06 Fix wiki link.
2019-11-07 Add OSH logo
2019-11-07 Update text
2019-11-07 Rename MultiplePrograms to Threads
2019-11-07 Change `PWM` to `LEDs`
2019-11-07 Add docs submodule
2019-11-07 Point Arduino instructions at the wiki.
2019-11-10 Update board images.
2019-11-10 Add LED count to API initialization.
2019-11-13 Cleanup ws2812b API
2019-11-13 Add ws2812b example to ChibiOS
2019-11-13 Add ws2812b example for Arduino
2019-11-13 Addressable LED README updates.
2019-11-13 Fix README link
2019-11-14 Update device in Makefiles
2019-11-15 Update gerbers.
2019-11-18 Update gerbers for alpha version 1a4
2019-11-19 Update charge indicator LED
2019-11-29 AddressableLED example for libopencm3
2019-12-01 Fix issue where last two LEDs don't get data.
2019-12-01 Use enum for output state.
2019-12-01 Update READMEs
2019-12-01 Add RunningLEDs to STM32Cube and libopencm3
2019-12-01 Simplify Running LEDs example for ChibiOS.
2019-12-02 Update hardware silkscreens
2019-12-04 Adjust resistors.
2019-12-31 Rename 18650 to "Standard"
2019-12-31 Add "mini" version
2020-01-18 Adjust space around battery terminals.
2020-01-18 Minor adjustments/text/icon
2020-01-18 Rename "Mini" to "Small"
2020-01-18 Fix spacing around battery clips.
2020-01-18 Update version number (1a2)
2020-01-19 Add "Tiny" version with 10440 battery
2020-01-19 Rename SCLK to SCK
2020-01-22 Update the image.
2020-01-22 Better description.
2020-01-25 Add "fp-info-cache" to git ignore and remove space in dir name.
2020-01-30 Use STM32F412CGUx (Regular & Tiny)
2020-01-30 Finish updating Small board with STM32F4
2020-01-30 Rename files to remove MCU name
2020-02-01 Update BOM & gerbers
2020-02-03 Update gerbers for pcbway
2020-02-03 Update gerbers with origins
2020-02-06 Update gerbers
2020-02-07 Update boms
2020-02-10 Convert some STM32Cube examples to F4xx
2020-02-12 Convert basic ChibiOS examples to F4
2020-02-12 Update libopencm3
2020-02-12 Update basic libopencm3 examples
2020-02-17 Add HSE crystal
2020-02-18 Add extra ground pin.
2020-02-22 Fresh gerbers
2020-03-08 Add fuel gauge.
2020-03-13 Add WS2812 timing.
2020-03-16 Updates for STM32F412
2020-03-17 Update fade to work with F4 chip.
2020-03-18 Add first circuitpython examle.
2020-03-19 CircuitPython readme.
2020-03-19 Update basic STM32Cube examples for F11 chip.
2020-03-19 Add comment.
2020-03-19 Change to STM32F11 chip.
2020-03-19 Update STM32 HAL libraries
2020-03-19 CircuitPython instructions.
2020-03-19 First pass at getting the AddressableLEDs working.
2020-03-19 Update instructions.
2020-03-21 Add CircuitPython examples.
2020-03-22 Add NVM support/example to circuitpython.
2020-03-22 Update readme.
2020-03-22 Cleanup copy.
2020-03-26 Update pins and arduino examples.
2020-03-26 Update pinout
2020-03-27 Fix dfu-util device targeting.
2020-03-27 Get addressable LED example working (STM32Cube)
2020-03-27 Cleanup addressable LED example.
2020-03-27 USB serial example (STM32)
2020-03-27 Remove fuel gauge example
2020-03-28 Get basic libopencm3 examples running on STM32F4
2020-03-28 Update Arduino USB example.
2020-03-28 Get basic ChibiOS examples working (STM32F4)
2020-04-12 Production boards.
2020-04-12 Update EEPROM example.
2020-04-12 Rename EEPROM example.
2020-04-12 Rename again.
2020-04-12 Update EEPROM libopencm3 example
2020-04-12 Fix ld file.
2020-04-12 Rename EEPROM-ish folder.
2020-04-13 Delete
2020-04-15 Fix addressable LEDs example in libopencm3
2020-04-15 Try to fix Addressable LEDs for Chibios (not working)
2020-04-15 Fix EEPROM example for Chibios.
2020-04-15 Fix USBSerial example for Chibios.
2020-04-15 Consolodate USB examples.
2020-04-15 Fix threads example.
2020-04-15 Clean up examples.
2020-04-18 Remove old addressable LEDs arduino example
2020-04-18 Fix Arduino addressable LEDs example.
2020-04-24 Checkpoint
2020-04-24 Remove AddressableLEDs from ChibiOS...for now
2020-04-24 Add old LED code (not working)
2020-07-02 Add flash chip
2020-07-02 Update READMEs to have more thorough information to getting started.
2020-07-04 Add tindie badge.
2020-07-13 Fix the chip number
2020-08-07 Compact version
2020-08-17 Update switch footprint.
2020-08-17 Add RGB LED & Flash. Change power switch.
2020-08-28 Checkpoint commit (v1.2a3)
2020-10-27 Add 4 PWM LEDs.
2020-11-18 New CircuitPython examples
2020-11-18 Circuit updates
2020-11-18 Add images.
2020-11-18 Update twinkle stars documentation.
2020-11-18 Add gifs to the Compact ThunderPack
2020-11-19 Cleanup and commit.
2020-11-19 Rename Standard -> Original
2020-11-19 Remove "Small" & "Tiny" hardware versions.
2020-11-19 Update KAN15 LED placement.
2020-11-20 Fix kicad references.
2020-11-20 Add new pinout diagrams.
2020-11-21 Update photos and README
2020-11-22 Minor updates
2020-11-22 Add autosaves to gitignore.
2020-11-22 v1.2
2020-11-22 ThunderPack v1.2 (#5)
    * Compact version (4cm x 1.9cm)
    * Onboard 16MB flash chip
    * Illuminated switch
    * RGB DotStar LED
    * New battery charger chip.
2020-11-22 Update breadboard photo.
2020-11-22 Typos
2020-11-22 Update chip specs.
2020-12-22 Add ESD. Update labeling
2021-01-27 Cleanup fills and labels.
2021-01-27 Prep for production.
